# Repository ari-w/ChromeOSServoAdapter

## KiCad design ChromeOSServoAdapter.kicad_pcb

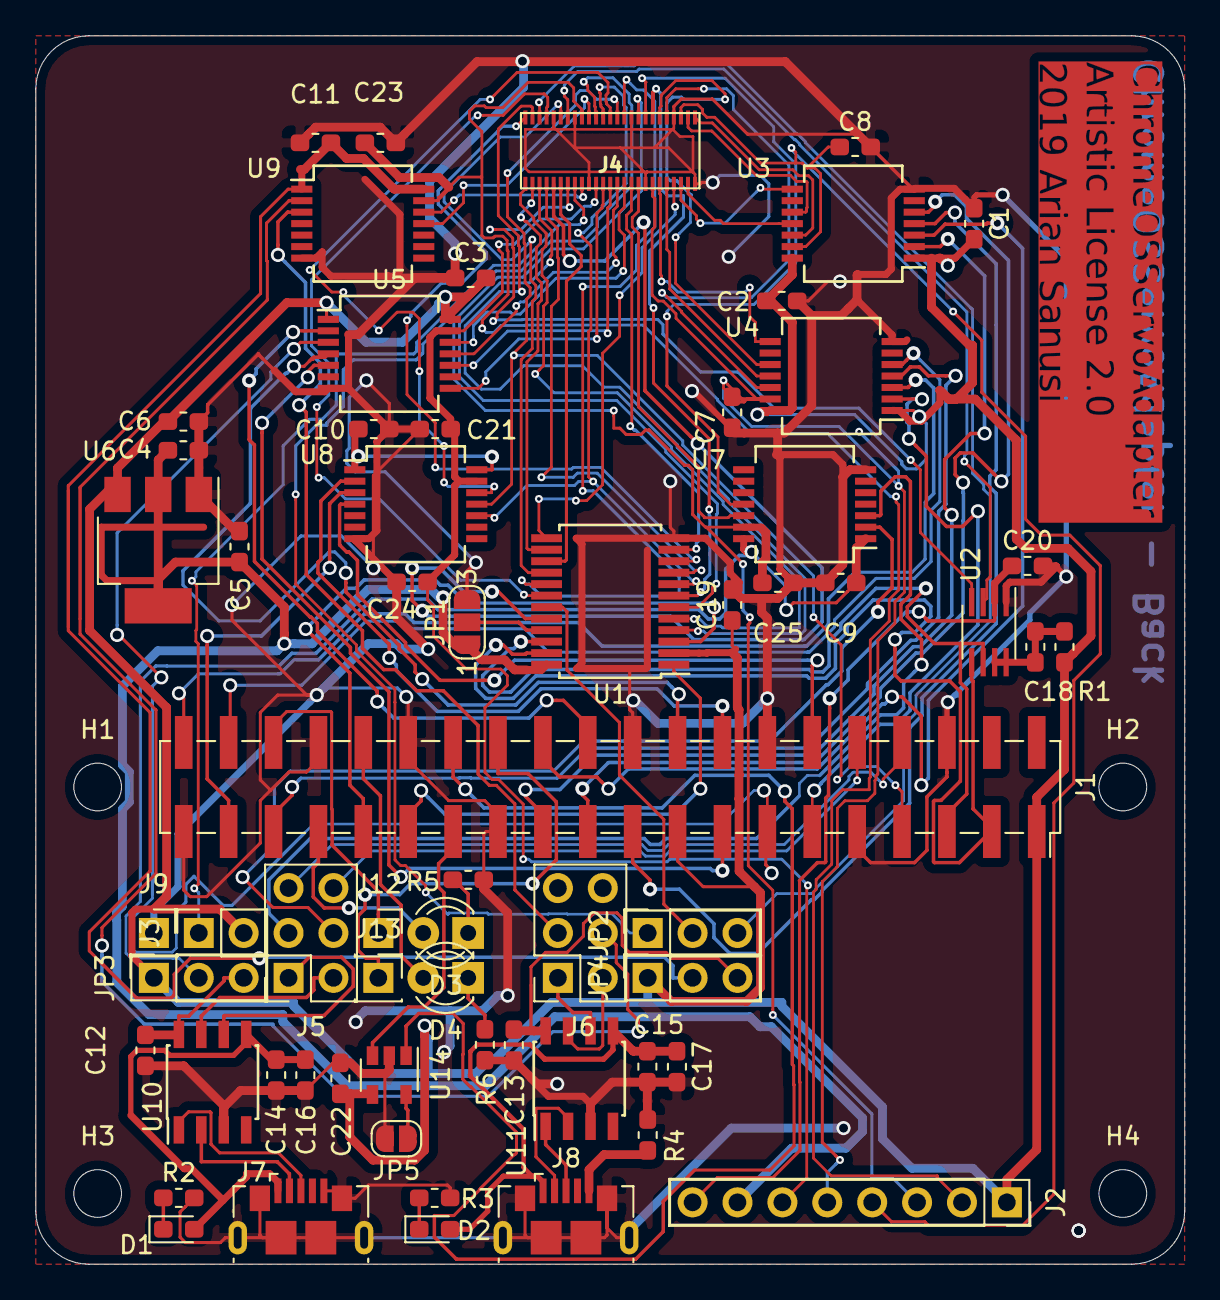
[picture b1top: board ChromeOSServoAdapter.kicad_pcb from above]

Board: 2 copper layers, 65.0 x 69.5 mm, 67 parts (0 on the bottom side), 102 nets.

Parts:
C1, C2, C3, C4, C7, C8, C9, C10, C11, C12, C13, C14, C15, C19, C20, C21, C22, C23, C24, C25: 10n; C_0603_1608Metric_Pad1.05x0.95mm_HandSolder
C5, C6, C16, C17: 10u; C_0603_1608Metric_Pad1.05x0.95mm_HandSolder
C18: 200p; C_0603_1608Metric_Pad1.05x0.95mm_HandSolder
D1, D2: LED; LED_0603_1608Metric_Pad1.05x0.95mm_HandSolder
D3, D4: LED; LED_D3mm
H1, H2, H3, H4: MountingHole; MountingHole_2.7mm_M2.5_ISO14580
J1: Raspberry_Pi_2_3; PinSocket_2x20_P2.54mm_Vertical_SMD
J2: Conn_01x08_Female; S1x8
J3: Conn_01x02_Female; S1x2
J4: Conn_02x25_Odd_Even; AXK850xxxWG
J5, J6: Conn_02x03_Odd_Even; S2x3
J7, J8: USB_B_Micro; USB_Micro-B_GCT_USB3076-30-A
J9, J12, J13: Conn_01x01_Female; S1x1
JP1: SolderJumper_3_Open; SolderJumper-3_P1.3mm_Open_RoundedPad1.0x1.5mm_NumberLabels
JP2, JP3, JP4: SolderJumper_3_Open; JP3
JP5: SolderJumper_2_Open; SolderJumper-2_P1.3mm_Open_RoundedPad1.0x1.5mm
R1: 200k; R_0603_1608Metric_Pad1.05x0.95mm_HandSolder
R2, R3, R5, R6: 1k; R_0603_1608Metric_Pad1.05x0.95mm_HandSolder
R4: 0; R_0603_1608Metric_Pad1.05x0.95mm_HandSolder
U1: TCA6416A; SSOP-24_5.3x8.2mm_P0.65mm
U2: PCA9306; SSOP-8_2.95x2.8mm_P0.65mm
U3, U4, U5, U7, U8, U9: NLSX5014G; SSOP-14_5.3x6.2mm_P0.65mm
U6: NCP1117-1.8_SOT223; SOT-223-3_TabPin2
U10, U11: CH330N; SOIC-8_3.9x4.9mm_P1.27mm
U14: AT24CS32-STUM; SOT-23-5

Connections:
/1v8: C4.1, C5.1, J2.7, JP1.1, U1.24, U6.2
/DUT_COLD_RESET_L: J4.38, U1.7
/DUT_DEV_MODE: J4.7, U1.9
/DUT_GOOG_REC_MODE_L: J4.22, JP2.1
/DUT_JTAG_RTCK: J4.26, U8.12
/DUT_JTAG_TCK_BUF: J4.29, U5.12
/DUT_JTAG_TDI_BUF: J1.7, J4.28, U8.11
/DUT_JTAG_TDO: J4.25, U5.10
/DUT_JTAG_TMS_BUF: J4.27, U5.11
/DUT_JTAG_TRST_L: J4.23, U5.8
/DUT_LID_OPEN: J4.8, U1.18
/DUT_MFG_MODE: J4.12, U1.16
/DUT_PWR_BUTTON: J4.30, U1.17
/DUT_RX1: J1.8, J5.5
/DUT_SPI1_CLK_BUF: J4.41, U4.11
/DUT_SPI1_CS_BUF: J4.42, U4.12
/DUT_SPI1_DI_BUF: J4.39, U4.8
/DUT_SPI1_DO: J4.40, U4.10
/DUT_SPI2_CLK_BUF: J4.50, U3.12
/DUT_SPI2_CS_BUF: J4.47, U3.11
/DUT_SPI2_DI_BUF: J4.48, U3.10
/DUT_SPI2_DO: J4.45, U3.8
/DUT_TX1: J1.10, J5.6
/DUT_WARM_RESET_L: J4.24, U1.8, U8.10
/FW_UP_L: J4.9, U1.20
/HPD: J4.11, U1.15
/I2C_REMODE_ADC_SCL: J4.14, U2.3
/I2C_REMOTE_ADC_SDA: J4.13, U2.4
/IntExtender: J1.29, U1.1
/JTAG_RTCK: J1.16, U8.2
/JTAG_TCK: J1.22, U5.2
/JTAG_TDI: J1.37, U8.3
/JTAG_TMS: J1.13, U5.3
/JTAG_TRST: J1.15, U5.5
/JTAG_WARM_RESET: J1.12, U8.4
/KBD_COL1: J4.6, JP2.3
/KBD_COL2: J4.3, U1.14
/KBD_ROW1: J4.4, U1.4
/KBD_ROW2: J4.1, U1.5
/KBD_ROW3: J4.2, U1.10
/PCH_DISABLE_L: J4.5, U1.6
/PP3300_R: J3.1, J4.15
/PPDUT_JTAG_VREF: C21.1, C24.1, J2.6, J4.21, U5.13, U8.13
/PPDUT_SPI1_VREF: C7.1, J2.5, J4.37, U4.13
/PPDUT_SPI2_VREF: C8.1, J2.4, J4.46, U3.13
/PPDUT_UART1_VREF: C23.1, J2.2, J4.18, U9.13
/PPDUT_UART2_VREF: C25.1, J2.3, J4.34, U7.13
/SCL: J1.5, U1.22, U2.6
/SDA: J1.3, U1.23, U2.5
/SD_DETECT_L: J4.31, U1.11
/SPI_HOLD_L: J4.43, U1.13
/TJAG_TDO: J1.18, U5.4
/UART1_DUT_SERVO_TX: J4.17, U9.12
/UART1_SERVO_DUT_TX: J4.20, U9.11
/UART2_DUT_SERVO_TX: J4.33, U7.12
/UART2_SERVO_DUT_TX: J4.36, U7.11
/VUSB1: C14.1, C16.1, D1.2, J7.1, U10.5
/VUSB2: C15.1, C17.1, D2.2, J8.1, U11.5
/resetExtendet: J1.31, U1.3
GND: C1.1, C2.1, C3.1, C4.2, C5.2, C6.2, C7.2, C8.2, C9.2, C10.2, C11.2, C12.2, C13.2, C14.2, C15.2, C16.2, C17.2, C19.2, C20.2, C21.2, C22.2, C23.2, C24.2, C25.2, J1.6, J1.9, J1.14, J1.20, J1.25, J1.30, J1.34, J1.39, J4.10, J4.16, J4.19, J4.32, J4.35, J4.44, J4.49, J7.5, J7.6, J8.6, J9.1, JP1.3, JP5.2, R2.2, R3.2, R4.2, R5.2, R6.2, U1.12, U2.1, U3.7, U4.7, U5.7, U6.1, U7.7, U8.7, U9.7, U10.3, U11.3, U14.2
unnamed: C9.1, JP3.2, U7.1, U7.14
unnamed: C10.1, U8.1, U8.14
unnamed: C11.1, JP4.2, U9.1, U9.14
unnamed: C12.1, JP3.3, U10.8
unnamed: C13.1, JP4.3, U11.8
unnamed: C18.1, C18.2, R1.2, U2.7, U2.8
unnamed: C20.1, J2.8, U2.2
unnamed: D1.1, R2.1
unnamed: D2.1, R3.1
unnamed: D3.1, R5.1
unnamed: D3.2, J1.33
unnamed: D4.1, R6.1
unnamed: D4.2, J1.32
unnamed: J1.11, U4.2
unnamed: J1.19, U3.4
unnamed: J1.21, U3.5
unnamed: J1.23, U3.2
unnamed: J1.24, U3.3
unnamed: J1.26, J13.1
unnamed: J1.27, U14.3
unnamed: J1.28, U14.1
unnamed: J1.35, U4.4
unnamed: J1.36, J12.1
unnamed: J1.38, U4.5
unnamed: J1.40, U4.3
unnamed: J5.1, U10.6
unnamed: J5.2, U10.7
unnamed: J5.3, U7.3
unnamed: J5.4, U7.2
unnamed: J6.1, U11.6
unnamed: J6.2, U11.7
unnamed: J6.3, U9.3
unnamed: J6.4, U9.2
unnamed: J7.2, U10.2
unnamed: J7.3, U10.1
unnamed: J8.2, U11.2
unnamed: J8.3, U11.1
unnamed: J8.5, R4.1
unnamed: JP1.2, U1.21
unnamed: JP2.2, U1.19
unnamed: JP5.1, U14.5
VCC: C1.2, C2.2, C3.2, C6.1, C19.1, C22.1, J1.1, J1.17, J2.1, J3.2, JP3.1, JP4.1, R1.1, U1.2, U3.1, U3.14, U4.1, U4.14, U5.1, U5.14, U6.3, U14.4

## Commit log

2019-05-01 initial: gitignore
2019-05-01 schematic should be complete, components placed on pcb and bypass capacitors routed
2019-05-01 removed redundant taps
2019-05-01 board intermediate
2019-05-04 board production ready
2019-05-04 gitignore gerber
2019-05-04 add license
